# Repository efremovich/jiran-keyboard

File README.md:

# Jiran Keyboard
Jiran is a 6x4 matrix ergo keyboard with additional 3 thumb and 1 pinky keys. 

Based on the [Jian](https://github.com/KGOH/Jian-Info) keyboard.

* __Author:__ [t.me/ladniys](https://t.me/ladniys) [u/Ladniy](https://reddit.com/u/Ladniy)
* __Layout:__ [keyboard-layout-editor.com](http://www.keyboard-layout-editor.com/#/gists/0547cd126f61f8c3f76b0a9952901da4)
* __Hardware Availability:__ open source, t.me/ladniys
* __Firmware:__ [QMK](https://github.com/Ladniy/qmk_firmware)
* __Building guide:__ not available yet
* __Parts (BOM):__

| Name           | Value         | Package           | Count        | Optional  | Comment            |
| :------------- | ------------: | :---------------- | -----------: | :-------- | :----------------- |
| Pro micro      | 5V 16MHz      |     17.78x33.02mm | 2            |           |                    |
| Switch         |               | MX/Alps/Choc      | 56           |           |                    |
| Diode          | 1N4148        | THT/SMD (SOD-123) | 56           |           |                    |
| Resistor       | 4.7k          | THT/SMD (0805)    | 2            |           | Must be placed on the master half |
| TRRS jack      |               | PJ-320A           | 2            |           | Optional if you're building only one half  
| Tact switch    |               | DIP 3X6X4,3mm     | 2            |  yes      |                    |
| Mosfet         | 2N7002        | SOT-123           | 2            |  yes      | Optional for LED's |
| Resistor       | 10k           | THT/SMD (0805)    | 2            |  yes      | Optional for LED's |
| Resistor       | 330           | THT/SMD (0805)    | 56           |  yes      | Optional for LED's |
| LED            |               | THT 1.8mm         | 56           |  yes      | Optional           |

 Supported by [MechChurch](https://t.me/s/mechchurch) community

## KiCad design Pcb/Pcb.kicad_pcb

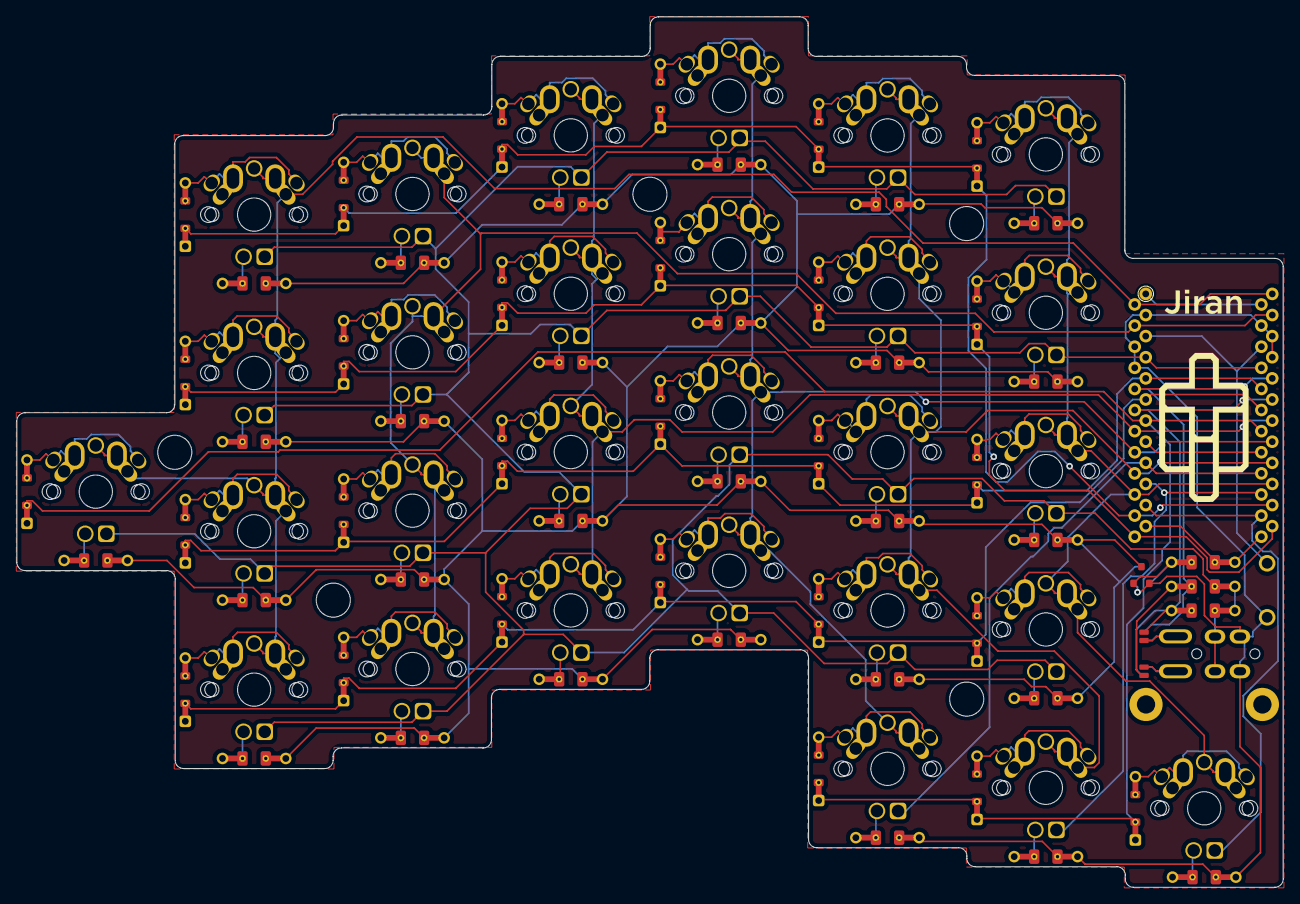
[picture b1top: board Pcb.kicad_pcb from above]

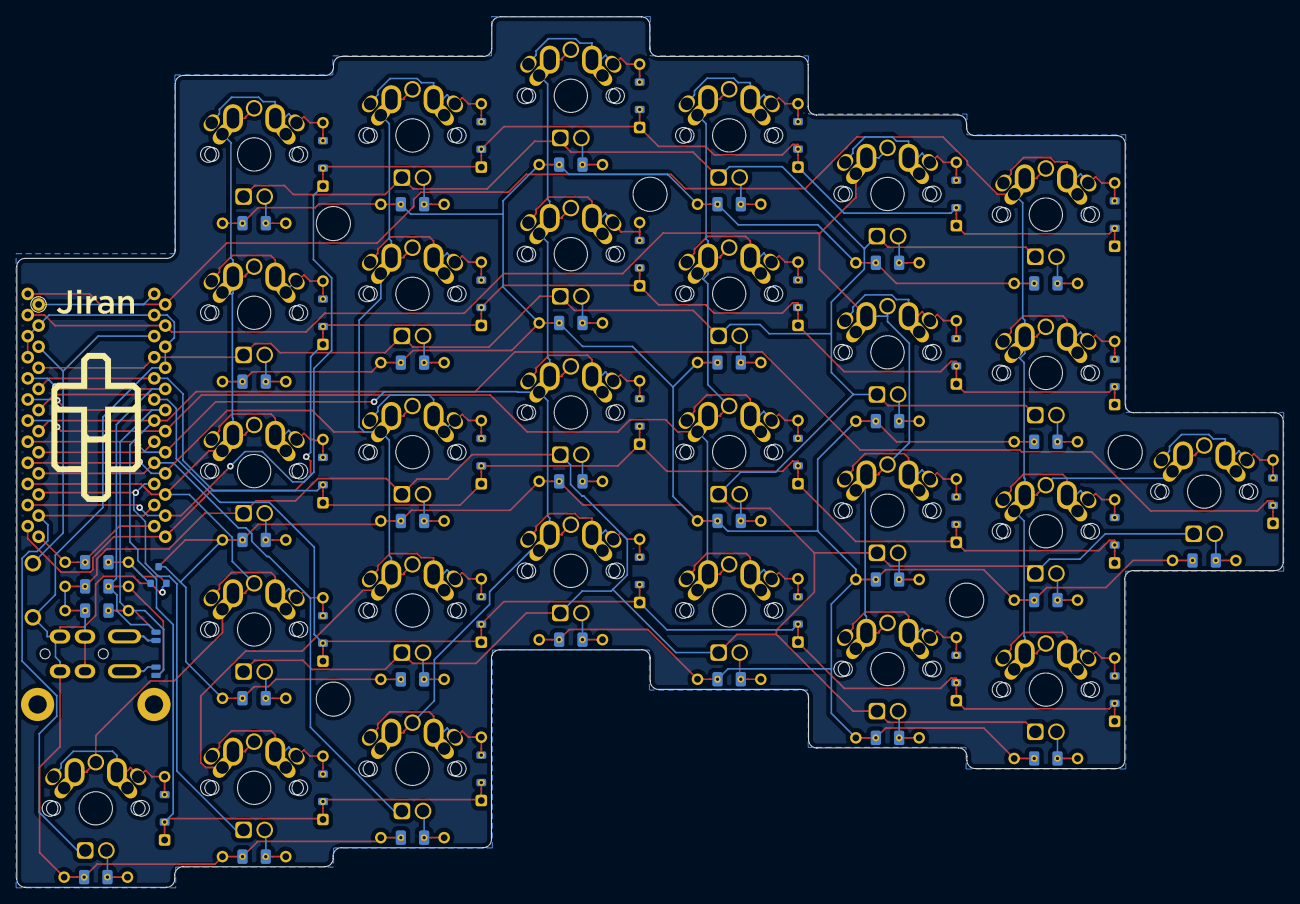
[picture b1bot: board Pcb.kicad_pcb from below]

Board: 2 copper layers, 152.3 x 104.7 mm, 132 parts (3 on the bottom side), 80 nets.

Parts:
D1, D2, D3, D4, D5, D6, D7, D8, D9, D10, D11, D12, D13, D14, D15, D16, D17, D18, D19, D20, D21, D22, D23, D24, D25, D26, D27, D28: 1N4148; Diode_Hybrid_SOD-123
D29, D30, D31, D32, D33, D34, D35, D36, D37, D38, D39, D40, D41, D42, D43, D44, D45, D46, D47, D48, D49, D50, D51, D52, D53, D54, D55, D56: LED_Small; LED
G1, G2: LOGO; Silk_Logo_Old
H1, H2, H3, H6, H7: CaseHole; MountHole
H8, H9: CoverHole
J1: TRRS; TRSS_DUAL_THT
JP2, JP3, JP4, JP5: Jumper; jumper
Q1: 2N7002; SOT-23
R1, R2, R3, R4, R5, R6, R7, R8, R9, R10, R11, R12, R13, R14, R15, R16, R17, R18, R19, R20, R21, R22, R23, R24, R25, R26, R27, R28: 330R; Resistor_Hybrid_1205
R29, R30: 4.7k; Resistor_Hybrid_1205
R31: 10k; Resistor_Hybrid_1205
SW1, SW3, SW4, SW5, SW6, SW7, SW8, SW9, SW10, SW11, SW12, SW13, SW14, SW15, SW16, SW17, SW18, SW19, SW20, SW21, SW22, SW23, SW24, SW25, SW26, SW27, SW28: SW_Push; Switch_MxAlpsChoc_MillMax_1u
SW2: SW2; Switch_MxAlpsChoc_MillMax_1u
SW29: SW_Push; Reset_Switch
U1: ProMicro; ProMicro_TwoSide

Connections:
/CAPS: D54.2, U1.16
/LED: R31.2, U1.13
/LEDOut: Q1.3, R1.2, R2.2, R3.2, R4.2, R5.2, R6.2, R7.2, R8.2, R9.2, R10.2, R11.2, R12.2, R13.2, R14.2, R15.2, R16.2, R17.2, R18.2, R19.2, R20.2, R21.2, R22.2, R23.2, R24.2, R25.2
/NUM: D56.2, U1.14
/SCROLL: D55.2, U1.15
/col0: SW1.2, SW7.2, SW13.2, SW19.2, SW25.2, U1.1
/col1: SW2.2, SW8.2, SW14.2, SW20.2, U1.2
/col2: SW3.2, SW9.2, SW15.2, SW21.2, U1.7
/col3: SW4.2, SW10.2, SW16.2, SW22.2, SW26.2, U1.8
/col4: SW5.2, SW11.2, SW17.2, SW23.2, SW27.2, U1.9
/col5: SW6.2, SW12.2, SW18.2, SW24.2, SW28.2, U1.10
/rowA: D1.1, D2.1, D3.1, D4.1, D5.1, D6.1, U1.11
/rowB: D7.1, D8.1, D9.1, D10.1, D11.1, D12.1, U1.12
/rowC: D13.1, D14.1, D15.1, D16.1, D17.1, D18.1, U1.20
/rowD: D19.1, D20.1, D21.1, D22.1, D23.1, D24.1, U1.19
/rowE: D25.1, D26.1, D27.1, D28.1, U1.18
GND: J1.B, Q1.2, R26.2, R27.2, R28.2, SW29.2, U1.3, U1.4, U1.23
unnamed: D1.2, SW1.1
unnamed: D2.2, SW2.1
unnamed: D3.2, SW3.1
unnamed: D4.2, SW4.1
unnamed: D5.2, SW5.1
unnamed: D6.2, SW6.1
unnamed: D7.2, SW7.1
unnamed: D8.2, SW8.1
unnamed: D9.2, SW9.1
unnamed: D10.2, SW10.1
unnamed: D11.2, SW11.1
unnamed: D12.2, SW12.1
unnamed: D13.2, SW13.1
unnamed: D14.2, SW14.1
unnamed: D15.2, SW15.1
unnamed: D16.2, SW16.1
unnamed: D17.2, SW17.1
unnamed: D18.2, SW18.1
unnamed: D19.2, SW19.1
unnamed: D20.2, SW20.1
unnamed: D21.2, SW21.1
unnamed: D22.2, SW22.1
unnamed: D23.2, SW23.1
unnamed: D24.2, SW24.1
unnamed: D25.2, SW25.1
unnamed: D26.2, SW26.1
unnamed: D27.2, SW27.1
unnamed: D28.2, SW28.1
unnamed: D29.1, R1.1
unnamed: D30.1, R2.1
unnamed: D31.1, R3.1
unnamed: D32.1, R4.1
unnamed: D33.1, R5.1
unnamed: D34.1, R6.1
unnamed: D35.1, R7.1
unnamed: D36.1, R8.1
unnamed: D37.1, R9.1
unnamed: D38.1, R10.1
unnamed: D39.1, R11.1
unnamed: D40.1, R12.1
unnamed: D41.1, R13.1
unnamed: D42.1, R14.1
unnamed: D43.1, R15.1
unnamed: D44.1, R16.1
unnamed: D45.1, R17.1
unnamed: D46.1, R18.1
unnamed: D47.1, R19.1
unnamed: D48.1, R20.1
unnamed: D49.1, R21.1
unnamed: D50.1, R22.1
unnamed: D51.1, R23.1
unnamed: D52.1, R24.1
unnamed: D53.1, R25.1
unnamed: D54.1, R26.1
unnamed: D55.1, R27.1
unnamed: D56.1, R28.1
unnamed: J1.A, JP2.1, JP3.1
unnamed: J1.D, JP4.1, JP5.1
unnamed: Q1.1, R31.1
RST: SW29.1, U1.22
SCL: JP3.2, JP5.2, R30.2, U1.6
SDA: JP2.2, JP4.2, R29.1, U1.5
VCC: D29.2, D30.2, D31.2, D32.2, D33.2, D34.2, D35.2, D36.2, D37.2, D38.2, D39.2, D40.2, D41.2, D42.2, D43.2, D44.2, D45.2, D46.2, D47.2, D48.2, D49.2, D50.2, D51.2, D52.2, D53.2, J1.C, R29.2, R30.1, U1.21

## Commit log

2019-10-19 Initialize project
2019-10-19 Finished with schematic and footprints
2019-10-19 Started work on pcb
2019-10-19 PCB update
2019-10-19 PCB route complete
2019-10-19 Postrout optimization
2019-10-20 Little Update
    Added hole's for mount, fixed some problems and created 3D design.
2019-10-20 Create a 3D case model.
2019-10-20 Adapted for 3D print case.
2019-10-21 Adapted for 3D case.
2019-10-22 Addapted for 3D case
2019-10-23 Eddit Silkscreen
2019-10-23 Created silkscreen-footprint
2019-10-23 Created Silkscreen reference
2019-10-23 Updated Silkscreen
2019-10-23 Silkscreen reference
2019-10-23 Update fp-info-cache
2019-10-24 Created gerber files
2019-10-24 Created ZIP archive with gerbers
2019-10-26 Created 3D case
2019-10-26 Added file for lasercut for case part
2019-10-26 Added file for laser cut for case part
2019-10-26 Created and fixed file for laser cut of acrylic case
2019-10-27 Added STL files for 3D print
2019-10-27 Removed Tracks
2019-10-27 Move dot's for other footprints
2019-10-27 Leds was rotated to north side
2019-10-27 Edited silkscreen
2019-10-27 Created new name silkscreen
2019-10-27 Created silkscreen for resistors value
2019-10-27 Removed silkscreen for rasistor value
2019-10-27 Update silkscreen
2019-10-27 Routed and filled
2019-10-27 Removed old gerbers
2019-10-27 Added new gerbers
2019-11-02 Fixed bug with I2C resistor's
2019-11-02 Unfill zones
2019-11-02 Deleted track's
2019-11-02 Moved diode
2019-11-02 Added support for Choc and Apls switche's
2019-11-03 Deleted ISP header
2019-11-03 Added LED's for lock indication
2019-11-03 Changed I2C jack
2019-11-03 Updated footprints
2019-11-03 Moved some parts
2019-11-04 Added hole's
2019-11-04 Placed hole in correct position
2019-11-04 Edited hole size
2019-11-04 Update
    Deleted silkscreen, moved jumpers and some components
2019-11-04 Remove (C)
2019-11-04 Reduced hole diameter
2019-11-04 Added silkscreen
2019-11-04 Redesigned case
2019-11-04 Created case for Jian mode
2019-11-04 Update
    Added tracks, edited silkscreen etc.
2019-11-04 Renamed
2019-11-04 Updated design for both mode
2019-11-05 Removed catalog with 3D print
2019-11-05 Removed
2019-11-05 Added link's for layouts
2019-11-05 Unfill all zones
2019-11-05 Updated jumper footprint
2019-11-05 Fill all zones
2019-11-05 Created new gerbers
2019-11-06 Import SES file
2019-11-06 Update Pcb.kicad_pcb-bak
2019-11-09 Update mosfet footprint
2019-11-09 Add holes for breakway numrow
2019-11-09 Remove old gerber
2019-11-09 Remove old silkscreen footprint
2019-11-09 Add new silkscreen
2019-11-09 New silkscreen file's
2019-11-09 Change polarity
2019-11-10 Route PCB
2019-11-10 Place track and fill all zones
2019-11-12 Create gerber files
2019-11-12 Add JLC silkscreen mark
2019-11-12 Move JLC silkscreen mark
2019-11-12 Create new gerbers files
2019-11-12 Create ZIP archive with gerbers
2019-11-13 Add CDR file for Jiran mode case
2019-12-16 Add CDR format file for Jian's mod case
2019-12-16 Add render of PCB
2019-12-18 Update hole footprints
2019-12-18 Add more break holes
2019-12-18 Update dsn file for new hole size
2019-12-18 Remove old logo silkscreen
2019-12-18 Remove hole for Jian mode
2019-12-18 Move hole for mount
2019-12-18 Route tracks
2019-12-19 Create support SMD package for footprints
2019-12-19 Move SOT
2019-12-19 Move pro micro footprint
2019-12-20 Update
    Remove old render, edit description, add building and BOM titles
2019-12-20 Complete bom table
2019-12-20 Add support millmax socket for swithes
2019-12-20 Change footprint
2019-12-20 Add millmax socket support
2019-12-20 Change hole size for spacer
2019-12-20 Route track
2019-12-20 Remove old pictures and silkscreen file
2019-12-20 Change logo for silkscreen
2019-12-20 Remove old gerbers
2019-12-20 Remove Jian case version
2019-12-20 Create new gerbers file
2019-12-20 Create new render
2019-12-20 Resize picture
2019-12-21 Add MechChurch logo
2019-12-21 Update MechChurch link
2019-12-21 Add author
2019-12-22 Move MechChurch link to the bottom
2019-12-22 Update format
2019-12-22 Add bom annotation
2020-01-22 Replace footprints
2020-01-22 Remove unuse footprints
2020-01-22 Rename and some fix
2020-01-22 Replace TRRS footprint
2020-01-22 Remove old version
2020-01-22 Rename
2020-01-22 Create new gerbers for old silkscreen
2020-01-22 Remove old gerber files
2020-01-22 Create new BMP and PSD silk files
2020-01-22 Add reference logo
2020-01-22 Add new footprints
2020-01-22 Remove unuse footprint
2020-01-22 Replace silk
2020-01-22 Replace render image
2020-01-22 Add link to QMK firmware
2020-01-25 Add corect value of diode
2020-01-25 Add corect value of resistors
2020-01-25 Add interactive BOM file for build
